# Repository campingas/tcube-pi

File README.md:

# tcube-pi

`tcube-pi` is the Raspberry Pi Zero 2 W runtime and local parent-admin service for T-Cube.

The repo owns child-facing button/audio behavior, local SQLite state, approved content playback, the Pi-hosted admin API, checked-in static admin UI output, Caddy/systemd deployment files, and Pi release-bundle packaging.

It does not own cloud services, Mac speech workers, hosted sync, or child-facing screen UI.

## Agent Entry

Coding agents should start with [AGENTS.md](AGENTS.md). It is the compact routing contract for default context, task-specific docs, validation gates, and repo-specific safety boundaries.

Use [VISION.md](VISION.md) for product constraints, [docs/tasks.md](docs/tasks.md) for active priorities, and [docs/developer/current-state.md](docs/developer/current-state.md) for the live implementation snapshot.

Use [docs/developer/README.md](docs/developer/README.md) to choose the focused developer doc for Rust, architecture, testing, branding, hardware, or install work.

## Quick Start

Install local development tools on macOS:

```bash
brew install rust just sqlite caddy
```

Run the Rust validation gate:

```bash
just check
just test
```

Run the keyboard simulator:

```bash
just run-device-sim
just run-device-sim-audio
```

Run the Pi-hosted admin service locally:

```bash
just run-pi-admin
```

In a second terminal, start local HTTPS for browser and phone testing:

```bash
just run-pi-admin-lan-caddy
```

Open `https://127.0.0.1:8443/` on the same machine or the printed `https://<lan-ip>:8443/` URL from a phone on the same network.

## Repository Map

- [src/](src/): Rust runtime, Pi admin service, and admin-load measurement harness.
- [content/](content/): default approved local content and audio assets.
- [admin-ui/](admin-ui/): Svelte + Vite source for the parent dashboard.
- [admin-ui/build/](admin-ui/build/): checked-in static dashboard build served by `tcube-pi-admin`.
- [deploy/pi-admin-caddy/](deploy/pi-admin-caddy/): Caddy and systemd files for the installed Pi admin service.
- [deploy/pi-runtime/](deploy/pi-runtime/): systemd and env files for the installed child-facing runtime.
- [deploy/pi-release/](deploy/pi-release/): release-bundle preparation and Pi installer scripts.
- [deploy/pi-zero-button-smoke/](deploy/pi-zero-button-smoke/): temporary one-button bench smoke payload.
- [docs/developer/](docs/developer/): routed architecture, testing, Rust, branding, and state docs.
- [docs/hardware/](docs/hardware/): hardware assembly and Raspberry Pi OS Lite install docs.

## Binaries

- `tcube-pi`: child-facing runtime and keyboard simulator.
- `tcube-pi-admin`: local admin API and static dashboard server.
- `tcube-pi-admin-measure`: latency harness for admin-load impact.

## Admin UI

Use Bun for every admin UI workflow. Prefer the `just` recipes unless you are working directly inside `admin-ui/`.

```bash
just install-admin-ui
just build-admin-ui
just check-admin-ui
just test-admin-ui-unit
just test-admin-ui-mobile
```

The Pi does not run Node or Bun. Release packaging copies built files from `admin-ui/build/`, so rebuild that directory after UI source changes.

## Pi Install And Release

Fresh Raspberry Pi OS Lite setup lives in [docs/hardware/pi-os-lite-install.md](docs/hardware/pi-os-lite-install.md).

Installed HTTPS, Caddy CA trust, and browser access details live in [deploy/pi-admin-caddy/README.md](deploy/pi-admin-caddy/README.md).

Release-bundle preparation and installer behavior live in [deploy/pi-release/README.md](deploy/pi-release/README.md).

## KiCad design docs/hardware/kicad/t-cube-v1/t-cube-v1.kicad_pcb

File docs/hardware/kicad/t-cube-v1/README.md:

# T-Cube V1 KiCad Project

Open `t-cube-v1.kicad_pro` in KiCad 10. The project contains a native connector-level schematic and a routed 65 mm × 56 mm, two-layer carrier PCB for the Raspberry Pi Zero 2 W, five MKE-M02 button modules, one MAX98357A amplifier module, and one 8-ohm speaker.

The Hshop products are assembled modules, so the carrier uses project-local connector footprints in `T_Cube.pretty` rather than attempting to reproduce their onboard circuits. Confirm the pin labels and physical pitch on the delivered modules before ordering or assembling the PCB.

## Connectors

| Reference | Device | Pin order |
| --- | --- | --- |
| `J1` | Raspberry Pi Zero 2 W J8 | Standard physical pins 1–40 |
| `J2`–`J6` | MKE-M02 buttons 1–5 | 1 `GND (-)`, 2 `+5V (+)`, 3 `S` |
| `J7` | MAX98357A module | 1 `VIN`, 2 `GND`, 3 `BCLK`, 4 `LRC`, 5 `DIN`, 6 `OUT+`, 7 `OUT-` |
| `J8` | 3 W, 8-ohm speaker | 1 `SPK+`, 2 `SPK-` |

The speaker output is differential. Neither speaker terminal may be connected to ground.

## GPIO Mapping

| Function | BCM GPIO | Pi physical pin |
| --- | ---: | ---: |
| Button 1 | GPIO5 | 29 |
| Button 2 | GPIO6 | 31 |
| Button 3 | GPIO17 | 11 |
| Button 4 | GPIO27 | 13 |
| Button 5 | GPIO16 | 36 |
| I2S BCLK | GPIO18 | 12 |
| I2S LRC | GPIO19 | 35 |
| I2S DIN | GPIO21 | 40 |

## Board Notes

- Board outline: 65 mm × 56 mm.
- Stackup: two copper layers, nominal 1.6 mm board thickness.
- Mounting: four 2.7 mm non-plated holes intended for M2.5 hardware.
- Power: bottom-layer `+5V` plane and top-layer ground plane.
- Signals: 0.35 mm traces; differential speaker traces are 0.50 mm.
- The Pi and module headers are through-hole footprints. Verify which board face each physical module must occupy before soldering sockets or pin headers.

## Validation

Validated with KiCad CLI 10.0.3 on 2026-06-20:

- ERC: 0 errors and 0 warnings.
- DRC: 0 violations and 0 unconnected items.
- Schematic/PCB parity: 0 issues.
- Board zones refilled and the project rendered successfully.

These checks validate the documented netlist and PCB rules, not the dimensions of the delivered Hshop breakout boards. Measure those boards and update the project-local footprints if their connector positions or mechanical clearances differ.

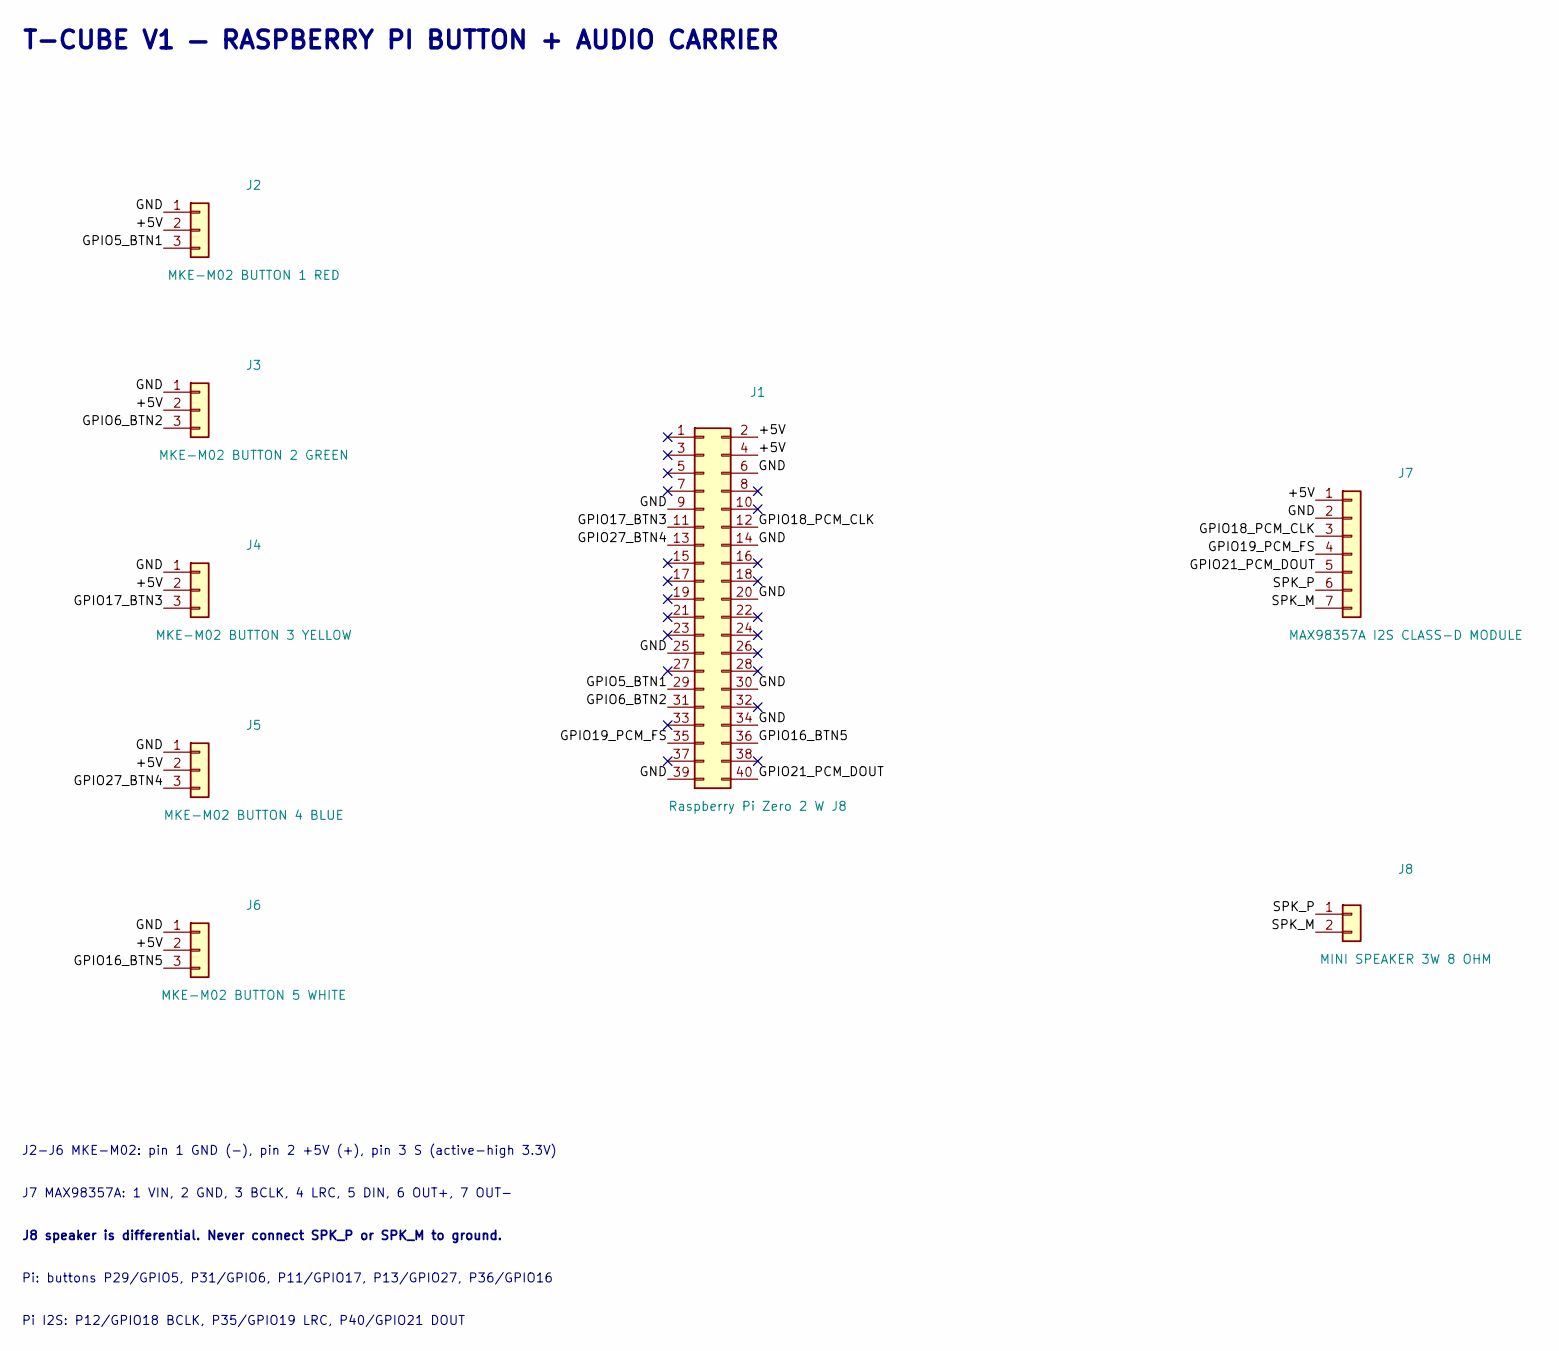
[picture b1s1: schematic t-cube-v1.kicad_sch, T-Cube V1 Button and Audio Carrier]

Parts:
J1: Raspberry Pi Zero 2 W J8; T_Cube_J1_2x20
J2: MKE-M02 BUTTON 1 RED; T_Cube_MKE_M02_1x03
J3: MKE-M02 BUTTON 2 GREEN; T_Cube_MKE_M02_1x03
J4: MKE-M02 BUTTON 3 YELLOW; T_Cube_MKE_M02_1x03
J5: MKE-M02 BUTTON 4 BLUE; T_Cube_MKE_M02_1x03
J6: MKE-M02 BUTTON 5 WHITE; T_Cube_MKE_M02_1x03
J7: MAX98357A I2S CLASS-D MODULE; T_Cube_MAX98357A_1x07
J8: MINI SPEAKER 3W 8 OHM; T_Cube_SPEAKER_1x02

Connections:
/+5V: J1.2, J1.4, J2.2 (+5V_+), J3.2 (+5V_+), J4.2 (+5V_+), J5.2 (+5V_+), J6.2 (+5V_+), J7.1 (VIN)
/GND: J1.6, J1.9, J1.14, J1.20, J1.25, J1.30, J1.34, J1.39, J2.1 (GND_-), J3.1 (GND_-), J4.1 (GND_-), J5.1 (GND_-), J6.1 (GND_-), J7.2 (GND)
/GPIO5_BTN1: J1.29, J2.3 (S)
/GPIO6_BTN2: J1.31, J3.3 (S)
/GPIO16_BTN5: J1.36, J6.3 (S)
/GPIO17_BTN3: J1.11, J4.3 (S)
/GPIO18_PCM_CLK: J1.12, J7.3 (BCLK)
/GPIO19_PCM_FS: J1.35, J7.4 (LRC)
/GPIO21_PCM_DOUT: J1.40, J7.5 (DIN)
/GPIO27_BTN4: J1.13, J5.3 (S)
/SPK_M: J7.7 (OUT-), J8.2 (SPK-)
/SPK_P: J7.6 (OUT+), J8.1 (SPK+)

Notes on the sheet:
T-CUBE V1 — RASPBERRY PI BUTTON + AUDIO CARRIER
J2-J6 MKE-M02: pin 1 GND (-), pin 2 +5V (+), pin 3 S (active-high 3.3V)
J7 MAX98357A: 1 VIN, 2 GND, 3 BCLK, 4 LRC, 5 DIN, 6 OUT+, 7 OUT-
J8 speaker is differential. Never connect SPK_P or SPK_M to ground.
Pi: buttons P29/GPIO5, P31/GPIO6, P11/GPIO17, P13/GPIO27, P36/GPIO16
Pi I2S: P12/GPIO18 BCLK, P35/GPIO19 LRC, P40/GPIO21 DOUT

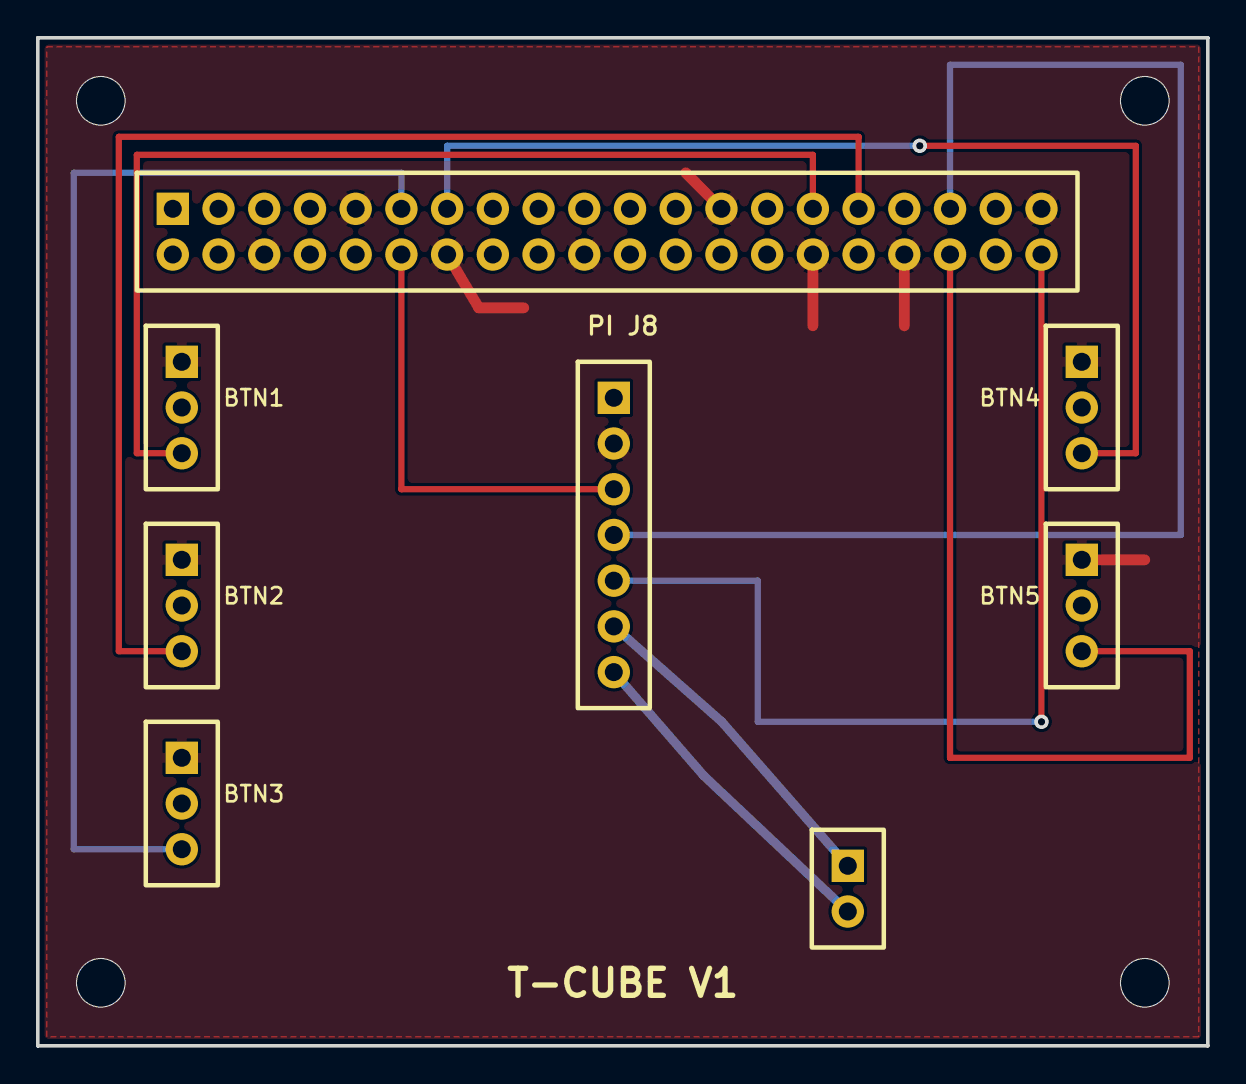
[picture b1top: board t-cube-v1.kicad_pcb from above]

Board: 2 copper layers, 65.0 x 56.0 mm, 12 parts (0 on the bottom side), 12 nets.

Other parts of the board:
MH1, MH2, MH3, MH4: M2.5; T_Cube_MountingHole_M2.5

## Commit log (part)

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2026-06-23 feat: tcube logic and admin-ui
2026-06-23 feat: add Rust config
2026-06-23 feat: add gh workflows
2026-06-23 ci: add pi release workflow and installer
2026-06-23 chore: prepare release v0.0.2
2026-06-29 feat: improved ui APIs
2026-06-29 feat: admin settings
2026-06-29 feat: factory reset
2026-06-30 feat: Axum coverage
2026-06-30 feat: server routes
2026-06-30 perf: optimize admin content and media paths
2026-06-30 chore: docker
2026-06-30 feat: add per-content play statistics
2026-06-30 feat: admin-ui optimisations
2026-06-30 feat: add unified recent activity feed
2026-06-30 fix: clean button config content lists
